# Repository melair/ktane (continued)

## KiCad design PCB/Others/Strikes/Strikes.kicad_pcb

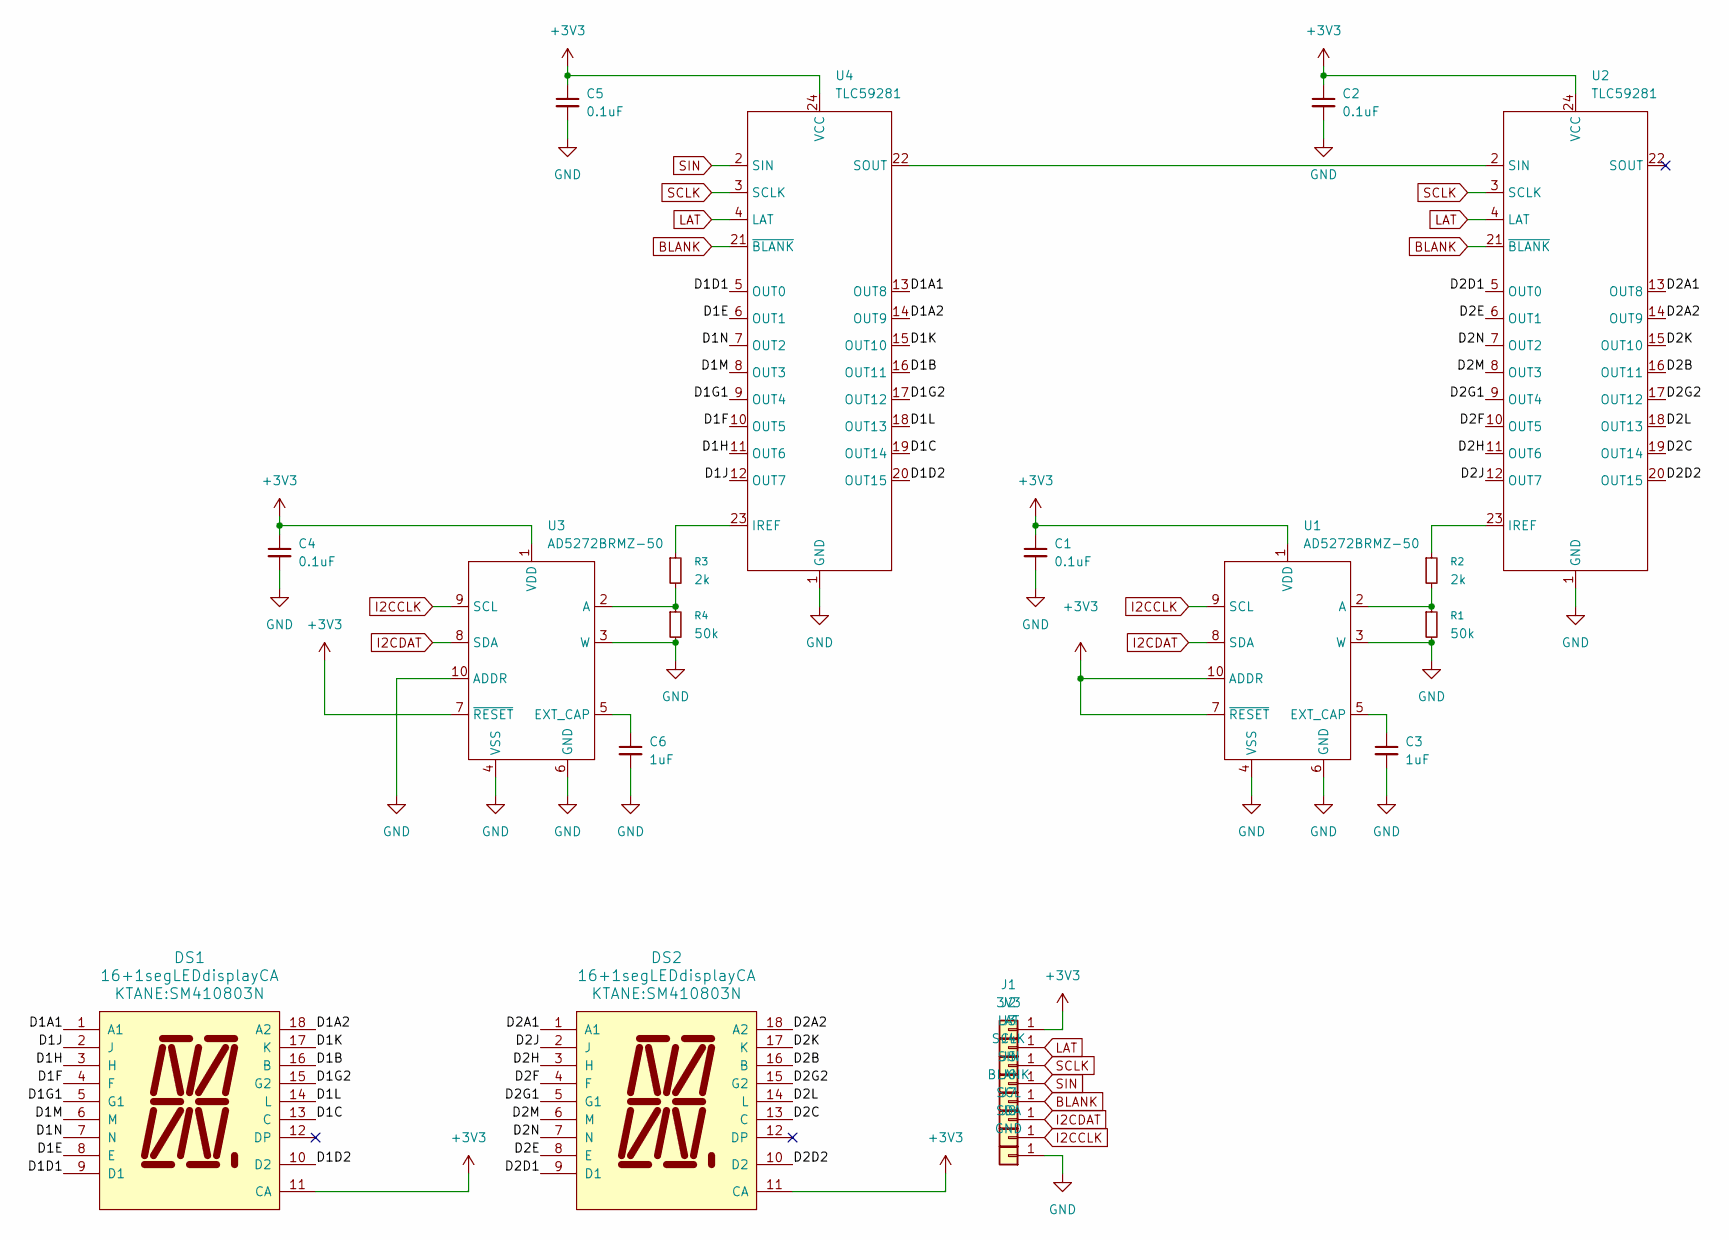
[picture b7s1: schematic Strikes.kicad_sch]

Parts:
C1, C2, C4, C5: 0.1uF; C_0603_1608Metric; DIGIKEY 1276-1005-1-ND
C3, C6: 1uF; C_0603_1608Metric; DIGIKEY 1276-1946-1-ND
DS1, DS2: 16+1segLEDdisplayCA; SM410803N; DIGIKEY STOCK/ALIEXPRESS
J1: 3V3; Pad4x2; DIGIKEY NONE
J2: LAT; Pad4x2; DIGIKEY NONE
J3: SCLK; Pad4x2; DIGIKEY NONE
J4: SIN; Pad4x2; DIGIKEY NONE
J5: BLANK; Pad4x2; DIGIKEY NONE
J6: SCL; Pad4x2; DIGIKEY NONE
J7: SDA; Pad4x2; DIGIKEY NONE
J8: GND; Pad4x2; DIGIKEY NONE
R1, R4: 50k; R_0603_1608Metric; DIGIKEY P51.0KHCT-ND
R2, R3: 2k; R_0603_1608Metric; DIGIKEY P2.00KHCT-ND
U1, U3: AD5272BRMZ-50; MSOP-10_3x3mm_P0.5mm; DIGIKEY 505-AD5272BRMZ-50-ND
U2, U4: TLC59281; SSOP-24_3.9x8.7mm_P0.635mm; DIGIKEY 296-25789-1-ND

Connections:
+3V3: C1.1, C2.1, C4.1, C5.1, DS1.11 (CA), DS2.11 (CA), J1.1, U1.1 (VDD), U1.7 (~RESET), U1.10 (ADDR), U2.24 (VCC), U3.1 (VDD), U3.7 (~RESET), U4.24 (VCC)
/D1A1: DS1.1 (A1), U4.13 (OUT8)
/D1A2: DS1.18 (A2), U4.14 (OUT9)
/D1B: DS1.16 (B), U4.16 (OUT11)
/D1C: DS1.13 (C), U4.19 (OUT14)
/D1D1: DS1.9 (D1), U4.5 (OUT0)
/D1D2: DS1.10 (D2), U4.20 (OUT15)
/D1E: DS1.8 (E), U4.6 (OUT1)
/D1F: DS1.4 (F), U4.10 (OUT5)
/D1G1: DS1.5 (G1), U4.9 (OUT4)
/D1G2: DS1.15 (G2), U4.17 (OUT12)
/D1H: DS1.3 (H), U4.11 (OUT6)
/D1J: DS1.2 (J), U4.12 (OUT7)
/D1K: DS1.17 (K), U4.15 (OUT10)
/D1L: DS1.14 (L), U4.18 (OUT13)
/D1M: DS1.6 (M), U4.8 (OUT3)
/D1N: DS1.7 (N), U4.7 (OUT2)
/D2A1: DS2.1 (A1), U2.13 (OUT8)
/D2A2: DS2.18 (A2), U2.14 (OUT9)
/D2B: DS2.16 (B), U2.16 (OUT11)
/D2C: DS2.13 (C), U2.19 (OUT14)
/D2D1: DS2.9 (D1), U2.5 (OUT0)
/D2D2: DS2.10 (D2), U2.20 (OUT15)
/D2E: DS2.8 (E), U2.6 (OUT1)
/D2F: DS2.4 (F), U2.10 (OUT5)
/D2G1: DS2.5 (G1), U2.9 (OUT4)
/D2G2: DS2.15 (G2), U2.17 (OUT12)
/D2H: DS2.3 (H), U2.11 (OUT6)
/D2J: DS2.2 (J), U2.12 (OUT7)
/D2K: DS2.17 (K), U2.15 (OUT10)
/D2L: DS2.14 (L), U2.18 (OUT13)
/D2M: DS2.6 (M), U2.8 (OUT3)
/D2N: DS2.7 (N), U2.7 (OUT2)
BLANK: J5.1, U2.21 (~BLANK), U4.21 (~BLANK)
GND: C1.2, C2.2, C3.2, C4.2, C5.2, C6.2, J8.1, R1.2, R4.2, U1.3 (W), U1.4 (VSS), U1.6 (GND), U2.1 (GND), U3.3 (W), U3.4 (VSS), U3.6 (GND), U3.10 (ADDR), U4.1 (GND)
I2CCLK: J7.1, U1.9 (SCL), U3.9 (SCL)
I2CDAT: J6.1, U1.8 (SDA), U3.8 (SDA)
LAT: J2.1, U2.4 (LAT), U4.4 (LAT)
unnamed: R1.1, R2.2, U1.2 (A)
unnamed: C3.1, U1.5 (EXT_CAP)
unnamed: R2.1, U2.23 (IREF)
unnamed: U2.2 (SIN), U4.22 (SOUT)
unnamed: R3.2, R4.1, U3.2 (A)
unnamed: C6.1, U3.5 (EXT_CAP)
unnamed: R3.1, U4.23 (IREF)
SCLK: J3.1, U2.3 (SCLK), U4.3 (SCLK)
SIN: J4.1, U4.2 (SIN)

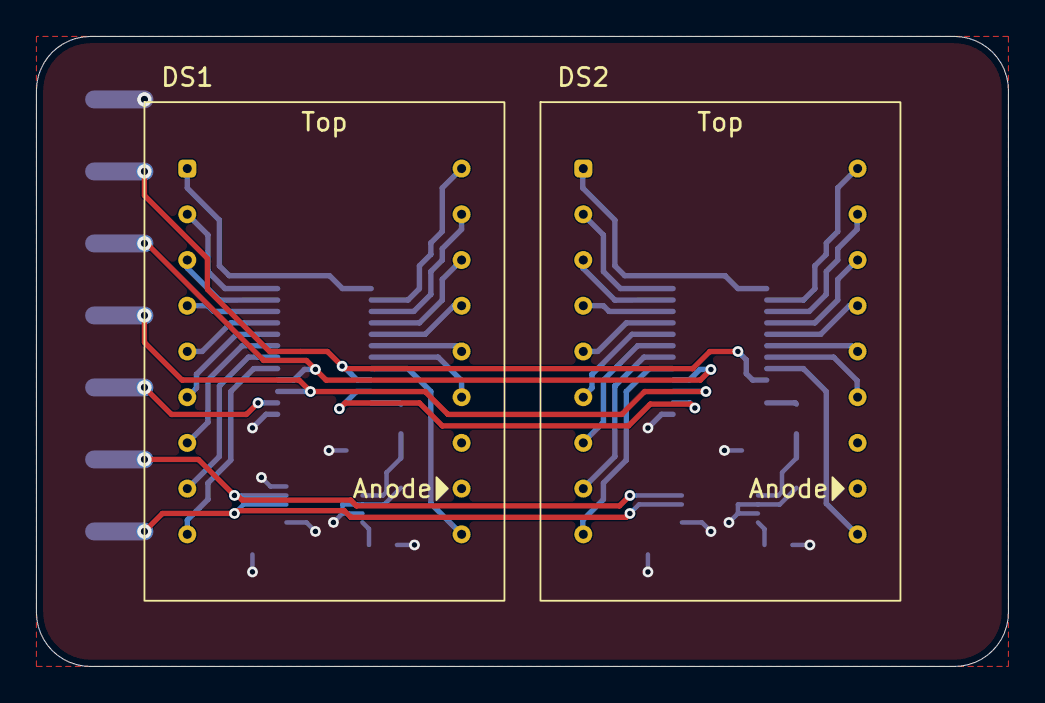
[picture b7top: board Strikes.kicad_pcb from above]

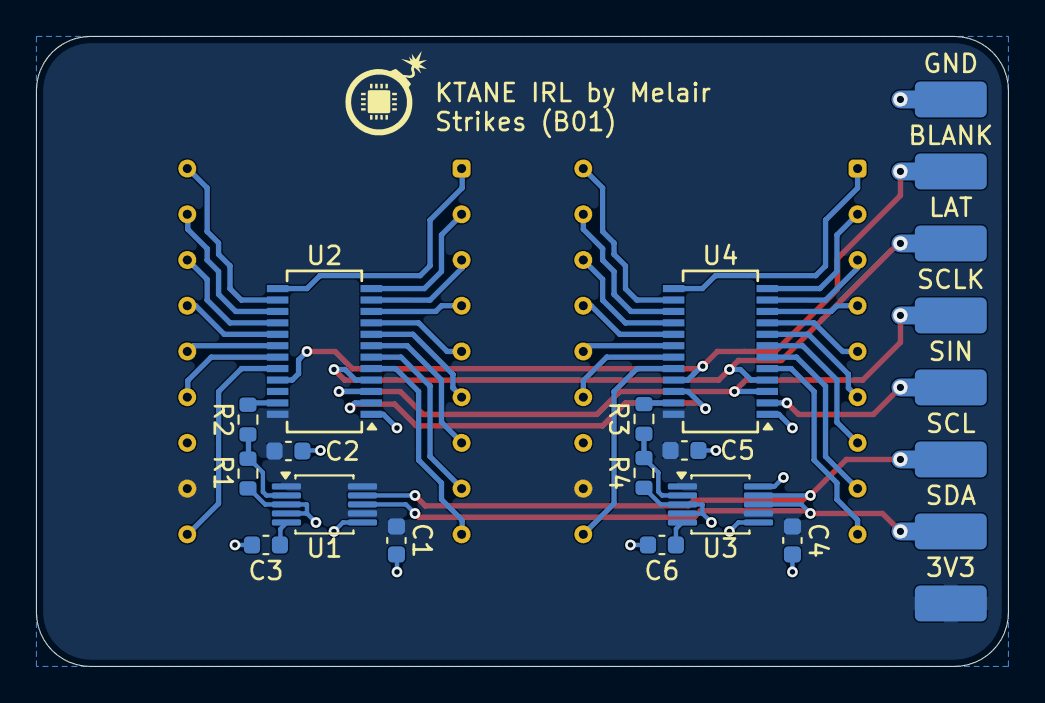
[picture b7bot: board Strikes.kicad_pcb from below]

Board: 2 copper layers, 54.0 x 35.0 mm, 24 parts (22 on the bottom side), 47 nets.

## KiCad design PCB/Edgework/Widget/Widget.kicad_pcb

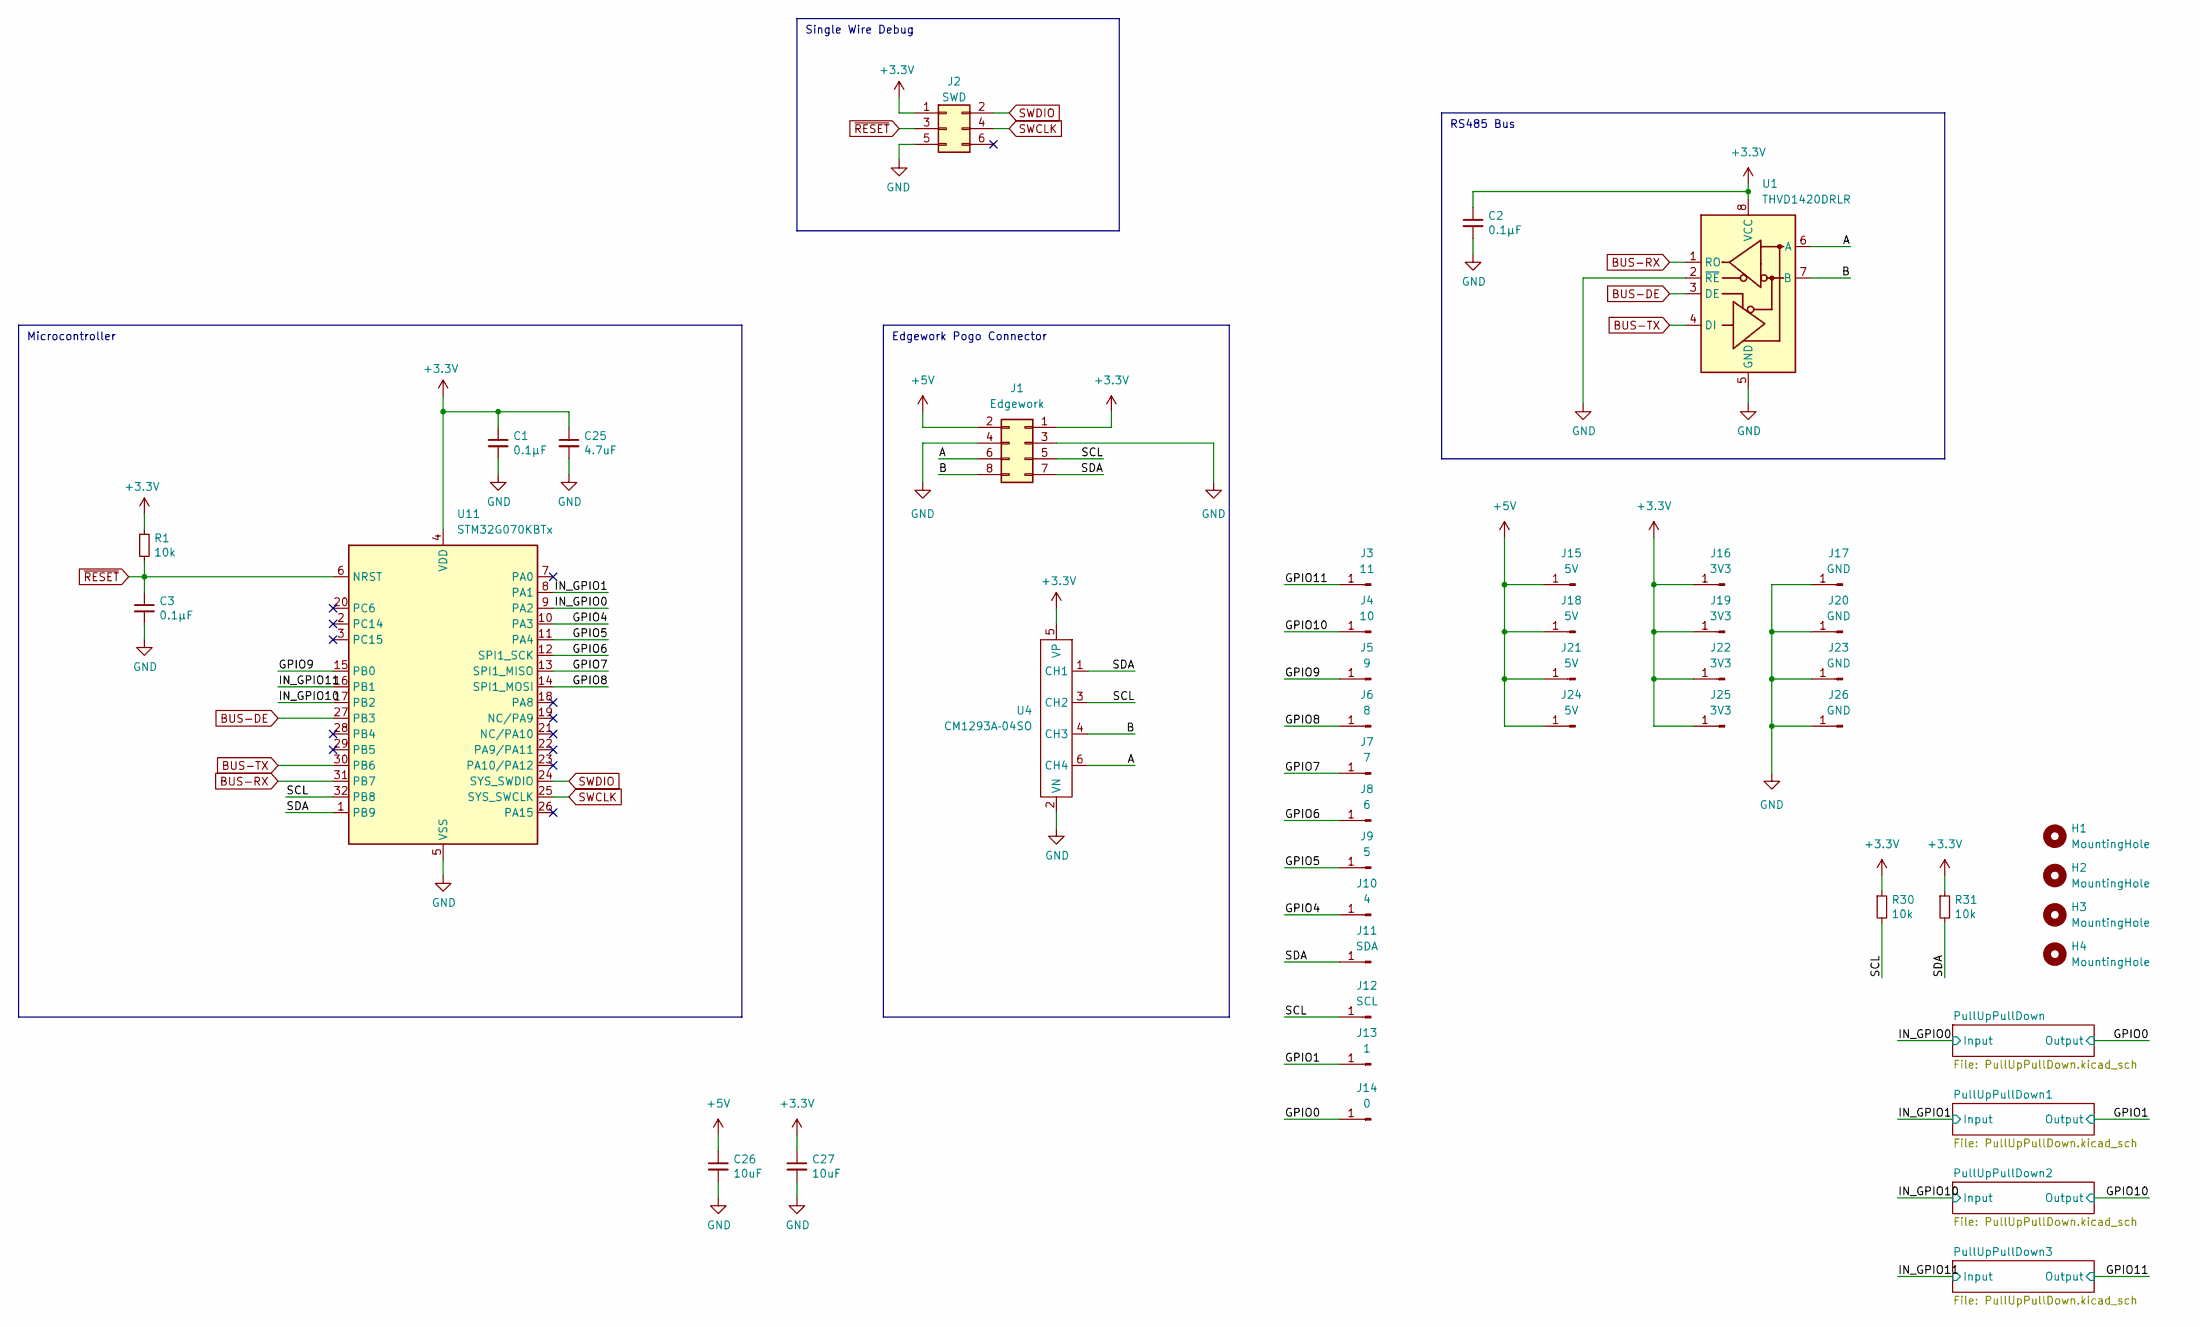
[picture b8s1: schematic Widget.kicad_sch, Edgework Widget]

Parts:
C1, C2, C3: 0.1μF; C_0603_1608Metric; DIGIKEY 1276-1005-1-ND
C25: 4.7uF; C_0603_1608Metric; DIGIKEY 1276-2087-1-ND
C26, C27: 10uF; C_0603_1608Metric; DIGIKEY 1276-1948-1-ND
H1, H2, H3, H4: MountingHole; MountingHole_3.2mm_M3_NoCopper; DIGIKEY NONE
J1: Edgework; PinHeader_2x04_P2.54mm_Horizontal; DIGIKEY STOCK/AliExpress
J2: SWD; Tag-Connect_TC2030-IDC-NL_2x03_P1.27mm_Vertical; DIGIKEY NONE
J3: 11; SolderPad; DIGIKEY NONE
J4: 10; SolderPad; DIGIKEY NONE
J5: 9; SolderPad; DIGIKEY NONE
J6: 8; SolderPad; DIGIKEY NONE
J7: 7; SolderPad; DIGIKEY NONE
J8: 6; SolderPad; DIGIKEY NONE
J9: 5; SolderPad; DIGIKEY NONE
J10: 4; SolderPad; DIGIKEY NONE
J11: SDA; SolderPad; DIGIKEY NONE
J12: SCL; SolderPad; DIGIKEY NONE
J13: 1; SolderPad; DIGIKEY NONE
J14: 0; SolderPad; DIGIKEY NONE
J15, J18, J21, J24: 5V; SolderPad; DIGIKEY NONE
J16, J19, J22, J25: 3V3; SolderPad; DIGIKEY NONE
J17, J20, J23, J26: GND; SolderPad; DIGIKEY NONE
R1, R30, R31: 10k; R_0603_1608Metric; DIGIKEY P10.0KHCT-ND
U1: THVD1420DRLR; SOT-583-8; DIGIKEY 296-THVD1420DRLRCT-ND
U4: CM1293A‐04SO; SC-74-6_1.55x2.9mm_P0.95mm; DIGIKEY CM1293A-04SOOSCT-ND
U11: STM32G070KBTx; LQFP-32_7x7mm_P0.8mm; DIGIKEY 497-STM32G070KBT6-ND

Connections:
+3.3V: C1.1, C2.1, C25.1, C27.1, J1.1, J2.1, J16.1 (Pin_1_1), J19.1 (Pin_1_1), J22.1 (Pin_1_1), J25.1 (Pin_1_1), R1.1, R30.1, R31.1, U1.8 (VCC), U4.5 (VP), U11.4 (VDD); also elsewhere on the board
+5V: C26.1, J1.2, J15.1 (Pin_1_1), J18.1 (Pin_1_1), J21.1 (Pin_1_1), J24.1 (Pin_1_1); also elsewhere on the board
/A: J1.6, U1.6 (A), U4.6 (CH4)
/B: J1.8, U1.7 (B), U4.4 (CH3)
/GPIO0: J14.1 (Pin_1_1); also elsewhere on the board
/GPIO1: J13.1 (Pin_1_1); also elsewhere on the board
/GPIO4: J10.1 (Pin_1_1), U11.10 (PA3)
/GPIO5: J9.1 (Pin_1_1), U11.11 (PA4)
/GPIO6: J8.1 (Pin_1_1), U11.12 (SPI1_SCK)
/GPIO7: J7.1 (Pin_1_1), U11.13 (SPI1_MISO)
/GPIO8: J6.1 (Pin_1_1), U11.14 (SPI1_MOSI)
/GPIO9: J5.1 (Pin_1_1), U11.15 (PB0)
/GPIO10: J4.1 (Pin_1_1); also elsewhere on the board
/GPIO11: J3.1 (Pin_1_1); also elsewhere on the board
/IN_GPIO0: U11.9 (PA2); also elsewhere on the board
/IN_GPIO1: U11.8 (PA1); also elsewhere on the board
/IN_GPIO10: U11.17 (PB2); also elsewhere on the board
/IN_GPIO11: U11.16 (PB1); also elsewhere on the board
/SCL: J1.5, J12.1 (Pin_1_1), R30.2, U4.3 (CH2), U11.32 (PB8)
/SDA: J1.7, J11.1 (Pin_1_1), R31.2, U4.1 (CH1), U11.1 (PB9)
BUS-DE: U1.3 (DE), U11.27 (PB3)
BUS-RX: U1.1 (RO), U11.31 (PB7)
BUS-TX: U1.4 (DI), U11.30 (PB6)
GND: C1.2, C2.2, C3.2, C25.2, C26.2, C27.2, J1.3, J1.4, J2.5, J17.1 (Pin_1_1), J20.1 (Pin_1_1), J23.1 (Pin_1_1), J26.1 (Pin_1_1), U1.2 (~RE), U1.5 (GND), U4.2 (VN), U11.5 (VSS); also elsewhere on the board
SWCLK: J2.4, U11.25 (SYS_SWCLK)
SWDIO: J2.2, U11.24 (SYS_SWDIO)
~RESET: C3.1, J2.3, R1.2, U11.6 (NRST)

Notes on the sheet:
Edgework Pogo Connector
Microcontroller
Single Wire Debug
RS485 Bus

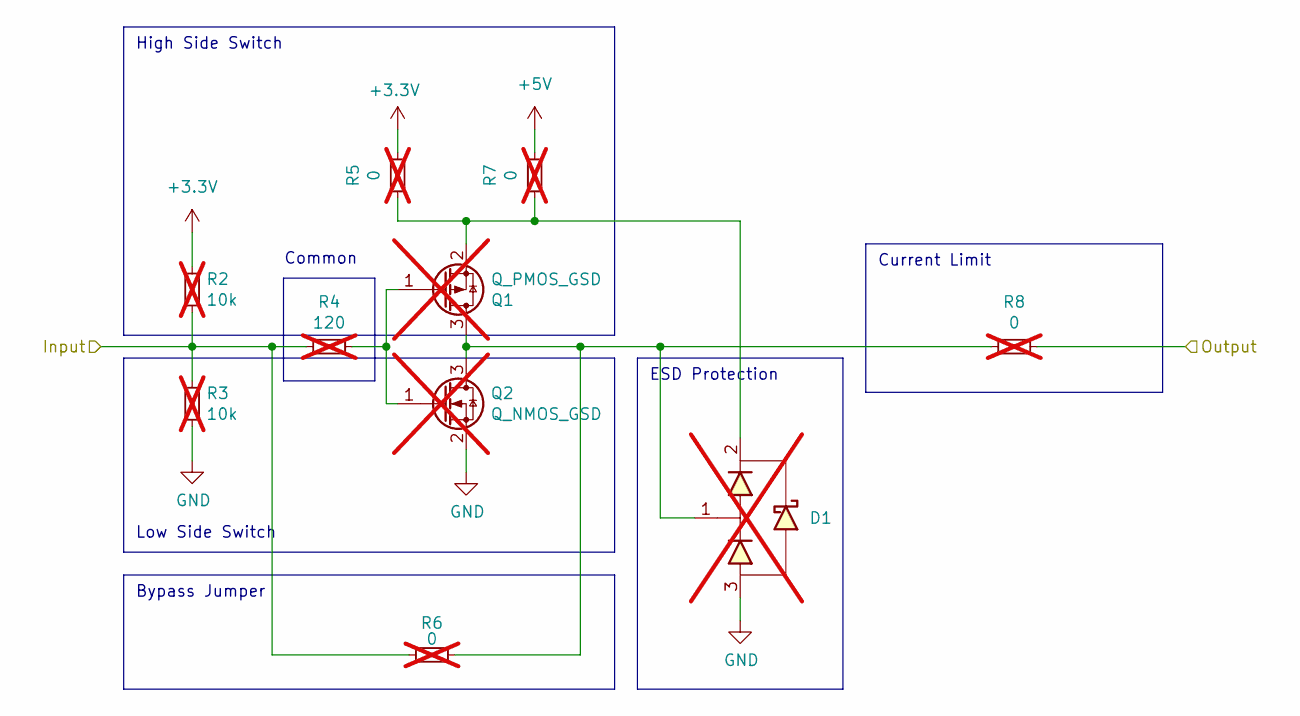
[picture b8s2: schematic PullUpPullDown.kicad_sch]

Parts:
D1: D1213A-01SO-7; SOT-23; DIGIKEY D1213A-01SO-7DICT-ND; not fitted
Q1: Q_PMOS_GSD; SOT-23; DIGIKEY DMG2301L-7DICT-ND; not fitted
Q2: Q_NMOS_GSD; SOT-23; DIGIKEY 31-DMN2310U-7CT-ND; not fitted
R2, R3: 10k; R_0603_1608Metric; DIGIKEY P10.0KHCT-ND; not fitted
R4: 120; R_0603_1608Metric; DIGIKEY P120HCT-ND; not fitted
R5, R6, R7, R8: 0; R_0603_1608Metric; DIGIKEY 10-ERJ-H3G0R00VCT-ND; not fitted

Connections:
+3.3V: R2.2, R5.1; also elsewhere on the board
+5V: R7.1; also elsewhere on the board
/GPIO0: R8.1; also elsewhere on the board
/IN_GPIO0: R2.1, R3.2, R4.1, R6.2; also elsewhere on the board
GND: D1.3, Q2.2 (S), R3.1; also elsewhere on the board
unnamed: D1.1, Q1.3 (D), Q2.3 (D), R6.1, R8.2
unnamed: Q1.1 (G), Q2.1 (G), R4.2
unnamed: D1.2, Q1.2 (S), R5.2, R7.2

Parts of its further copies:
D2, D3, D4: D1213A-01SO-7; SOT-23; DIGIKEY D1213A-01SO-7DICT-ND; not fitted
Q3, Q5, Q7: Q_PMOS_GSD; SOT-23; DIGIKEY DMG2301L-7DICT-ND; not fitted
Q4, Q6, Q8: Q_NMOS_GSD; SOT-23; DIGIKEY 31-DMN2310U-7CT-ND; not fitted
R9, R10, R16, R17, R23, R24: 10k; R_0603_1608Metric; DIGIKEY P10.0KHCT-ND; not fitted
R11, R18, R25: 120; R_0603_1608Metric; DIGIKEY P120HCT-ND; not fitted
R12, R13, R14, R15, R19, R20, R21, R22, R26, R27, R28, R29: 0; R_0603_1608Metric; DIGIKEY 10-ERJ-H3G0R00VCT-ND; not fitted

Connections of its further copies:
+3.3V: R9.2, R12.1, R16.2, R19.1, R23.2, R26.1; also elsewhere on the board
+5V: R14.1, R21.1, R28.1; also elsewhere on the board
/GPIO1: R15.1; also elsewhere on the board
/GPIO10: R22.1; also elsewhere on the board
/GPIO11: R29.1; also elsewhere on the board
/IN_GPIO1: R9.1, R10.2, R11.1, R13.2; also elsewhere on the board
/IN_GPIO10: R16.1, R17.2, R18.1, R20.2; also elsewhere on the board
/IN_GPIO11: R23.1, R24.2, R25.1, R27.2; also elsewhere on the board
GND: D2.3, D3.3, D4.3, Q4.2 (S), Q6.2 (S), Q8.2 (S), R10.1, R17.1, R24.1; also elsewhere on the board
unnamed: D2.1, Q3.3 (D), Q4.3 (D), R13.1, R15.2
unnamed: Q3.1 (G), Q4.1 (G), R11.2
unnamed: D2.2, Q3.2 (S), R12.2, R14.2
unnamed: D3.1, Q5.3 (D), Q6.3 (D), R20.1, R22.2
unnamed: Q5.1 (G), Q6.1 (G), R18.2
unnamed: D3.2, Q5.2 (S), R19.2, R21.2
unnamed: D4.1, Q7.3 (D), Q8.3 (D), R27.1, R29.2
unnamed: Q7.1 (G), Q8.1 (G), R25.2
unnamed: D4.2, Q7.2 (S), R26.2, R28.2

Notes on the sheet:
High Side Switch
Current Limit
Bypass Jumper
ESD Protection
Low Side Switch
Common

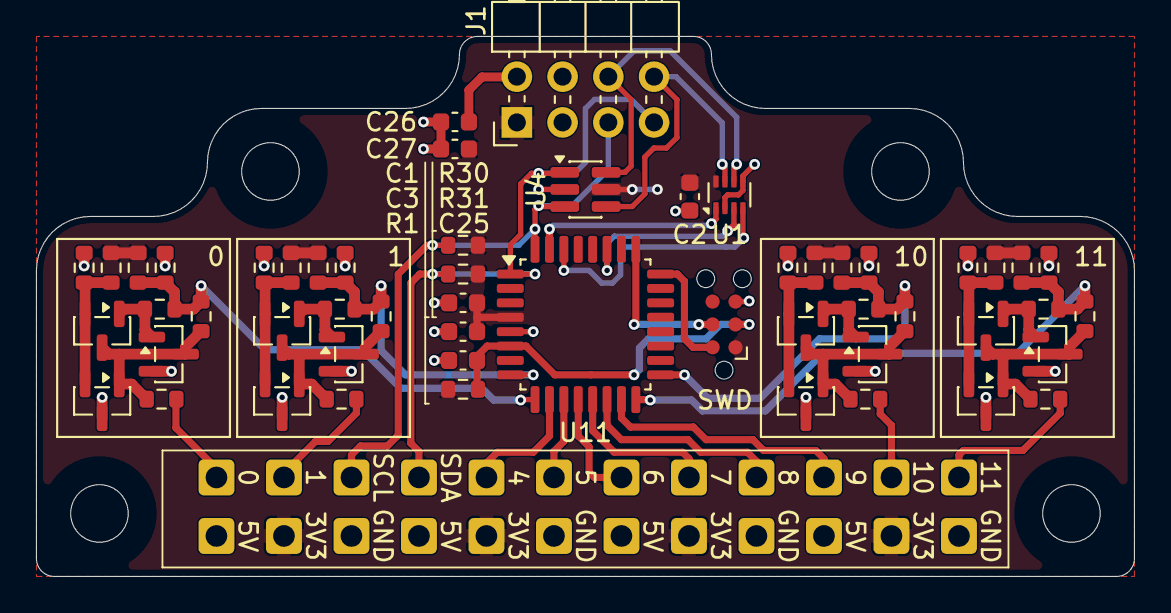
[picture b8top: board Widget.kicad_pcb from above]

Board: 4 copper layers, 61.0 x 30.0 mm, 82 parts (0 on the bottom side), 39 nets.

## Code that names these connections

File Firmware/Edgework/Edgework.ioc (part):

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Mcu.Name=STM32G070KBTx
Mcu.Package=LQFP32
Mcu.UserName=STM32G070KBTx
PA1.GPIOParameters=GPIO_Label
PA1.GPIO_Label=GPIO1
PA1.Signal=GPIO_Output
PA13.Mode=Serial_Wire
PA13.Signal=SYS_SWDIO
PA14-BOOT0.Mode=Serial_Wire
PA14-BOOT0.Signal=SYS_SWCLK
PA2.GPIOParameters=GPIO_Label
PA2.GPIO_Label=GPIO0
PA2.Signal=GPIO_Output
PA3.GPIOParameters=GPIO_Label
PA3.GPIO_Label=GPIO4
PA3.Signal=GPIO_Output
PA4.GPIOParameters=GPIO_Label
PA4.GPIO_Label=GPIO5
PA4.Signal=GPIO_Output
PA5.Mode=Full_Duplex_Master
PA5.Signal=SPI1_SCK
PA6.Mode=Full_Duplex_Master
PA6.Signal=SPI1_MISO
PA7.Mode=Full_Duplex_Master
PA7.Signal=SPI1_MOSI
PB0.GPIOParameters=GPIO_Label
PB0.GPIO_Label=GPIO9
PB0.Signal=GPIO_Output
PB1.GPIOParameters=GPIO_Label
PB1.GPIO_Label=GPIO11
PB1.Signal=GPIO_Output
PB2.GPIOParameters=GPIO_Label
PB2.GPIO_Label=GPIO10
PB2.Signal=GPIO_Output
PB3.Mode=Hardware Flow Control (RS485)
PB3.Signal=USART1_DE
PB6.Mode=Asynchronous
PB6.Signal=USART1_TX
PB7.Mode=Asynchronous
PB7.Signal=USART1_RX
PB8.Mode=I2C
PB8.Signal=I2C1_SCL
PB9.Mode=I2C
PB9.Signal=I2C1_SDA
RCC.HSE_VALUE=8000000
RCC.SYSCLKFreq_VALUE=64000000
RCC.SYSCLKSource=RCC_SYSCLKSOURCE_PLLCLK
board=custom

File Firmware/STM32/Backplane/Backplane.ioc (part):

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Mcu.Name=STM32G070KBTx
Mcu.Package=LQFP32
Mcu.UserName=STM32G070KBTx
PA0.GPIOParameters=GPIO_Label
PA0.GPIO_Label=REAR_UART_TX
PA0.Mode=Asynchronous
PA0.Signal=USART4_TX
PA1.GPIOParameters=GPIO_Label
PA1.GPIO_Label=REAR_UART_RX
PA1.Mode=Asynchronous
PA1.Signal=USART4_RX
PA10.GPIOParameters=GPIO_Label
PA10.GPIO_Label=FRONT_UART_RX
PA10.Mode=Asynchronous
PA10.Signal=USART1_RX
PA11\ [PA9].GPIOParameters=GPIO_Label
PA11\ [PA9].GPIO_Label=FRONT_EFUSE_FLT
PA11\ [PA9].Signal=GPIO_Input
PA12\ [PA10].GPIOParameters=GPIO_Label
PA12\ [PA10].GPIO_Label=FRONT_EFUSE_EN
PA12\ [PA10].Signal=GPIO_Output
PA13.Mode=Serial_Wire
PA13.Signal=SYS_SWDIO
PA14-BOOT0.Mode=Serial_Wire
PA14-BOOT0.Signal=SYS_SWCLK
PA2.GPIOParameters=GPIO_Label
PA2.GPIO_Label=REAR_BOOT
PA2.Signal=GPIO_Output
PA3.GPIOParameters=GPIO_Label
PA3.GPIO_Label=REAR_ILM
PA3.Mode=IN3
PA3.Signal=ADC1_IN3
PA4.GPIOParameters=GPIO_Label
PA4.GPIO_Label=BOOT
PA4.Signal=GPIO_Input
PA5.GPIOParameters=GPIO_Label
PA5.GPIO_Label=BUS_TX
PA5.Mode=Asynchronous
PA5.Signal=USART3_TX
PA6.GPIOParameters=GPIO_Label
PA6.GPIO_Label=STATUS_LED
PA6.Signal=GPIO_Output
PA8.GPIOParameters=GPIO_Label
PA8.GPIO_Label=FRONT_MODULE_DETECT
PA8.Signal=GPIO_Input
PA9.GPIOParameters=GPIO_Label
PA9.GPIO_Label=FRONT_UART_TX
PA9.Mode=Asynchronous
PA9.Signal=USART1_TX
PB0.GPIOParameters=GPIO_Label
PB0.GPIO_Label=BUS_RX
PB0.Mode=Asynchronous
PB0.Signal=USART3_RX
PB1.GPIOParameters=GPIO_Label
PB1.GPIO_Label=BUS_DE
PB1.Mode=Hardware Flow Control (RS485)
PB1.Signal=USART3_DE
PB2.GPIOParameters=GPIO_Label
PB2.GPIO_Label=FRONT_ILM
PB2.Mode=IN10
PB2.Signal=ADC1_IN10
PB6.Mode=I2C
PB6.Signal=I2C1_SCL
PB7.Mode=I2C
PB7.Signal=I2C1_SDA
PB9.GPIOParameters=GPIO_Label
PB9.GPIO_Label=REAR_EFUSE_FLT
PB9.Signal=GPIO_Input
PC14-OSC32_IN\ (PC14).GPIOParameters=GPIO_Label
PC14-OSC32_IN\ (PC14).GPIO_Label=REAR_EFUSE_EN
PC14-OSC32_IN\ (PC14).Signal=GPIO_Output
PC15-OSC32_OUT\ (PC15).GPIOParameters=GPIO_Label
PC15-OSC32_OUT\ (PC15).GPIO_Label=REAR_MODULE_DETECT
PC15-OSC32_OUT\ (PC15).Signal=GPIO_Input
PC6.GPIOParameters=GPIO_Label
PC6.GPIO_Label=FRONT_BOOT
PC6.Signal=GPIO_Output
RCC.HSE_VALUE=8000000
RCC.SYSCLKFreq_VALUE=64000000
RCC.SYSCLKSource=RCC_SYSCLKSOURCE_PLLCLK
board=custom

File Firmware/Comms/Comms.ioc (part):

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Mcu.Name=STM32WB09KEVx
Mcu.Package=VFQFPN32
Mcu.UserName=STM32WB09KEVx
PA0.Mode=I2C
PA0.Signal=I2C1_SCL
PA1.Mode=I2C
PA1.Signal=I2C1_SDA
PA11.Mode=Full_Duplex_Slave
PA11.Signal=SPI3_MOSI
PA2.Mode=Serial_Wire
PA2.Signal=DEBUG_SWDIO
PA3.Mode=Serial_Wire
PA3.Signal=DEBUG_SWCLK
PA8.Mode=Full_Duplex_Slave
PA8.Signal=SPI3_MISO
PA9.Mode=NSS_Signal_Hard_Input
PA9.Signal=SPI3_NSS
PB0.Mode=WakeUp0
PB0.Signal=PWR_WKUP0
PB12.Mode=LSE-External-Oscillator
PB12.Signal=RCC_OSC32_OUT
PB13.Mode=LSE-External-Oscillator
PB13.Signal=RCC_OSC32_IN
PB14.Mode=Clock-out
PB14.Signal=RCC_MCO
PB2.GPIOParameters=GPIO_Label
PB2.GPIO_Label=BLE_INT
PB2.Signal=GPIO_Input
PB3.Mode=Full_Duplex_Slave
PB3.Signal=SPI3_SCK
PB4.GPIOParameters=GPIO_Label
PB4.GPIO_Label=CAL_IN
PB4.Signal=S_TIM2_CH1
PB5.GPIOParameters=GPIO_Label
PB5.GPIO_Label=RUN
PB5.Signal=GPIO_Output
PB6.Mode=Asynchronous
PB6.Signal=LPUART1_TX
PB7.Mode=Asynchronous
PB7.Signal=LPUART1_RX
RCC.HSE_VALUE=32000000
RCC.SYSCLKSource=RCC_SYSCLKSOURCE_DIRECT_HSE
board=custom

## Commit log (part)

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2021-08-17 Add ARGB led strip for whos on first stages.
2021-08-19 Fix additional parameter.
2021-08-25 Update Password keymatrix and mapping.
2021-08-25 Fix bug with game seed being reset every time a status message was received.
2021-08-25 Rework wires to use standard colours, and functions to calculate the solution. Unimplemented.
2021-08-25 Add mode name lookup table and function.
2021-08-25 Minor whitespace formatting.
2021-08-27 Align new wire adc values correctly.
2021-08-27 Change Simon Says to be full brightness but turn off light on beep.
2021-08-27 For demoing only show serial number on the 1604 display.
2021-08-27 Misc changes and firmware version bump.
2021-09-01 Add noise on completion of module, add results on LCD screen after completing or failing.
2021-09-01 Add needy flag and common function for detecting if all enabled modules that aren't needy are done.
2021-09-02 Add keys needy module.
2022-08-26 Rework wire detection to only care about disconnections, not colour changes during play.
2022-08-30 Various KiCad file upgrades.
2022-09-04 Tweak maximum number of modules online, fix mode count.
2022-09-16 Remove blank module code.
2022-09-16 Add NVM functionality to read/write to the program space.
2022-09-16 Add .gitignore for KiCad backups.
2022-09-16 Add KiCad 6 project files.
2022-09-16 Refactor CAN address protocol to generic network, tidy up old blank references.
2022-09-16 Add missed OPCODE refactor.
2022-12-18 New module with RTC, uSD card and nf24 radio, all using SPI.
2022-12-18 Add gerbers used to produce Power Management board.
2023-02-05 Allow users of keymatrix to specify debounce samples.
2023-02-05 Add operator module, fix issue with time display when timer runs out.
2023-02-05 Add operator acrylic.
2023-02-05 Update .gitignroe.
2023-02-05 Add missing ui files.
2023-02-05 Add missing reference to stdbool.h
2023-02-12 Add UI for controller for debug, fix up bugin error handling, lint whitespace.
2023-02-12 Remove math.h to save program space.
2023-02-12 Only initialise LCD display if module uses it.
2023-02-15 Migrate specific module memory for ARGB to their own mode data struct.
2023-02-15 Move LCD into peripherals.
2023-02-15 Add missing else.
2023-02-20 First untested pass at SPI controller.
2023-02-20 Remove double space.
2023-02-21 Migrate SPI to use new KPORT.
2023-02-21 Add start of cardscan module.
2023-02-27 Add images for CardScan cards.
2023-02-27 Add card scan image readme.
2023-03-03 Split apart cardscan into logical pieces.
2023-03-04 Add cooldown for card reads based on UID at 2.5s, new cards can be read instantly due to new UID.
2023-03-04 Fix LCD number display, refactor module data into mode_data.
2023-03-04 Add ability to invoke special functions from controller to module, migrate cardscan.
2023-03-06 First pass at card scan module complete, readd ability to start game via UI, expose defining new characters for LCD.
2023-03-06 Add missed memory updates for Card Scan.
2023-03-07 Remove debug module.
2023-03-07 Add game completion logic handling for enabled modules.
2023-03-08 Add handling for enable/disable, shift cardscan programming to IDLE only phase.
2023-03-09 Fix up handling of state changes.
2023-03-09 Add support for disabling modules.
2023-03-10 Migrate ARGB to SPI abstraction, add delayed CS, initial opts work.
2023-03-11 Bump firmware version.
2023-03-13 Fix up SPI HAL to be more scalable, move pins into HAL. Implement RTC clock reading on optional module.
2023-03-26 Rework audio mixing to rely on service loop, optomise sample mixing, ensure audio fill request timer fires interrupt to wake from sleep.
2023-03-27 Add better tooling for sd card, add sdcard resources, updates FAT docs, add port usage tracking.
2023-03-27 Fix tab in bootloader.c
2023-03-27 Add framework for flasher firmware, offset at 0x01F000, for #13.
2023-03-27 Update pack.
2023-03-27 Migrate existing firmware to new location and rename.
2023-03-27 Remove static from mode function list.
2023-03-27 Remove mux play command, used for testing, accidentally committed.
2023-03-30 Share device config between programs, add version of firmware to end of program space.
    Using asm() is a hack to work around consts not being available in the bootloader,
    it makes some sense to unify the approach long term. Functions will have to be
    written to extract firmware versions using the NVM access routines.
2023-03-31 Extract NVM routines out to common directory, fix bug with eeprom.
    Previous initialisation of the EEPROM could result in a power off after the version
    is written but before the migration, resulting it 0xff data being returned rather
    than the migrated data.
    Move version set to after migrations.
2023-03-31 Optomise version location selection, saves 20 bytes.
2023-04-01 Flesh out new firmware functions.
2023-04-02 Minor comment fix.
2023-04-02 Remove restriction of controllers being only source of firmware, use nvm_*() functions in fw.c.
2023-04-04 Update CAN to send smaller messages if it needs to.
2023-04-05 Complete structure definitions of packets.
2023-04-09 Reimplement the firmware flasher. Add logic back to module code to start firmwaring.
2023-04-09 Fix bug with firmware updating, where it would ALWAYS firmware.
2023-04-12 Revert changes to packet handling, fix firmwaring. Fix a few bugs.
    Move packet handling back to things that are in the call tree, otherwise things
    are corrupted.
    Fix issues with enablement of modules, identify messages.
2023-04-12 Fix forced strike bug, adjust simon timings to be closer to game.
2023-04-15 Penny's Changes
2023-04-16 Add additional direction arrows to manual.
2023-04-16 Fix maximum number of supported strikes.
    Previously strikes 6 and 7 would result in excessively stretched time.
2023-04-16 Create generic functions for determining number of solved/enabled modules/puzzles.
2023-04-16 Migrate more module counting to use module_ functions.
2023-04-16 Remove initialisation for battery value.
2023-04-21 Add config UI for opts.
2023-04-23 Fix round one of compiler issues.
2023-04-25 Replace buzzer calls with start of sound system.
2023-05-07 Add needed sounds for existing modules.
2023-08-03 Migrate audio output to H-bridge over DAC.
2023-08-20 Fix bugs around opt setting, add DSP volume adjustment, fix FAT bugs.
2023-08-24 Fix up sounds, add DAC volume, fix power mgmt and display.
2023-08-25 Tidy up cardscan, fix bugs in audio, power display.
    Add module acrylic templates too.
2023-08-29 Rework of operator module, untested.
2023-08-29 Convert all KiCad to 6.0, clean up libraries, remove files that shouldn't be committed.
2023-08-29 Add .gitignore for PCB file types.
2023-08-29 Upgrade KiCad files from 6.0 to 7.0.
2023-09-03 Fix combined image configuration after migration to 2.41.
2023-09-03 Update module port usage.
2023-09-03 Add debug handling to packet handler.
2024-08-26 Update PIC18 SDK and compiler.
2024-08-26 Fix up support for debug packets.
2024-08-26 Fix extremely broken power status display logic.
2026-03-13 Remove legacy PCBs from V1.
2026-03-13 Update libraries to new V2 layouts.
2026-03-13 ControlBoard B02, with buck regulator fix.
2026-03-13 First pass of PCB rework.
2026-03-13 Add audio module.
2026-03-13 Add manual page for Ending the World.
2026-03-13 Add timer display and strike display.
2026-03-13 WIP: LCD Driver for Maze.
2026-03-13 WIP: Power management.
2026-03-13 Update gitignore for macos.
2026-03-14 Add initial VS Code MPLAB projects for Bootloader and ControlBoard.
2026-03-16 Add common library, fleshout basic bootloader.
2026-03-16 Define application locations via defines, add readme's with more info.
2026-03-18 Add basic MCU init, interrupt init, and pin HAL.
2026-03-20 First pass of FSM.
2026-03-21 First pass at SPI hal, however is huge once compiled.
2026-03-21 Rework SPI to only allow single instantiation, but take SPI port from compiler micro. 65% smaller build.
2026-03-22 Fix up SPI HAL, read and write appear to work.
2026-03-23 Add ability to repeat write buffer, useful for initialising large data.
2026-03-24 First pass at initialising ePaper screen.
2026-03-24 Add operations files.
2026-03-24 Generify stacking commands and data to the epaper screen.
2026-03-25 Correctly implement rotation, and fix up fill operation.
2026-03-25 Fix up comments.
2026-03-25 More work on rotation logic, preparing to move to a canvas selections state.
2026-03-25 Correct rotation 180.
2026-03-26 Generify operations to use common canvas setup.
2026-03-27 Fix up power LEDs on regulators.
2026-03-28 WIP: Correct displaying of program constants.
2026-03-28 WIP: Rework x2/y2 into width/height.
2026-03-29 Add 2FA LCD display pcb.
2026-03-31 Include all corrections, mint new gerbers. Update some to KiCad 10.
2026-04-08 Tidy project files, add new PIC for backplane, start backplane basis.
2026-04-09 Basic power handling with eFuse.
2026-04-11 Add I2C HAL abstraction.
2026-04-11 Update SPI state names to remove clashes, ensure pins are only configured if present.
2026-04-11 Add I2C to backplane.
2026-04-11 Test I2C in edgework.
2026-04-11 Tidy up Edgework, add serial label and font to Common.
2026-04-11 Fix up I2C to protect against edge conditions.
2026-04-11 Make spi_transaction_t not mutated, add guards.
2026-04-11 Remove legacy debug, improve timer ticks, prevent bootloader jumping to invalid application.
2026-04-11 Make access to internal_tick in timer atomic.
2026-04-11 Add mermaid diagram for i2c.
2026-04-11 WIP: ARGB implementation.
2026-04-12 First working pass at ARGB support.
2026-04-12 Remove fs_t name, fix corruption bug in argb_set.
2026-04-13 Add initialisation for control board, add/fix ARGB for control board.
2026-04-14 Add support for setting current via I2C.
2026-04-14 Add base support for status indicator, to be expanded later.
2026-04-17 More CSP work, add testing for strikes.
2026-04-17 Add support for SPI CLK polarity.
2026-04-18 Remove strike testing.
2026-04-18 Add TX and RX implementations for CSP system, including callback.
2026-04-18 Add more metrics, catch deadlock and runts.
2026-04-19 Don't power control board from programmer anymore.
2026-04-23 Fix deadlock after single CAN node running. Other safety tweaks.
2026-04-23 Add RNG and unique ID code.
2026-04-27 Add implementation for status/button control, plus keymatrix.
2026-04-27 Fix up minor bugs and typos.
2026-04-28 Clean up object init, add COBS implementation (untested) to CSP.
2026-04-29 Update to KiCad 10.
2026-05-01 Add template modes for other modes.
2026-05-23 End of PIC18 development for firmware, migration to STM32 hardware will occur.
2026-06-24 feat: Rework ControlBoard to use an STM32H562VGT6.
2026-06-25 feat: Upgrade backplane to a STM32G070KB.
2026-06-25 feat: Migrate edgework to a STM32G070KBT6.
2026-06-25 feat: Update audio board to consume I2S from STM32 parent board, removing ESP32.
2026-06-26 feat: Add support for battery for RTC on comms board.
2026-06-26 feat: Remove backup battery for RTC, and crystal. 1PPS can be derived from HSE.
2026-06-27 fix: Correct stitching for 3.3V and GND layers.
2026-06-27 chore: Add updated project.
2026-06-27 feat: Initial start of STM32 projects for firmware.
2026-06-27 feat: Configure initial peripherals on STM32H5.
2026-06-27 feat: Configure RTC clock from HSE.
2026-06-27 feat: Clock bus UART off of 32MHz HSI.
2026-06-27 feat: Export new revision BOM, allow in .gitignore, fix up revisions in schematics.
2026-06-27 feat: Replace bare pads for battery with a cell, incase we want to use a cell holder.
2026-06-27 feat: Final traces sizes for comms, final gerber exports.
2026-06-28 feat: Add peripheral config to other three MCUs.
2026-06-28 feat: Add submodule ports as basic GPIO outputs.
